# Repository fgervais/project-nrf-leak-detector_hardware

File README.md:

# Leak Detector, revision 3

Any two conductors can be connected to the screw terminals and the alarm will 
start if water shorts them out.

- [Complete Project](#complete-project)
- [PCB](#pcb)
- [Water Probe](#water-probe)
- [Power Consumption](#power-consumption)
- [Firmware](#firmware)
- [Notifications](#notifications)

## Complete Project

### Front side

### Back side

## PCB

### Front side

### Back side

## Water Probe

## Power Consumption

Based on revision [`8f98e931fbc428e85092b7998ec07682605cf380`](https://github.com/fgervais/project-nrf-leak-detector/tree/8f98e931fbc428e85092b7998ec07682605cf380/app/src).

### Idle

How long can the device monitor for a leak?

- Energizer CR2032 = $810 \\, C$
- Idle consumption = $1.09 \\, \frac{{\mu}C}{s}$

```math
\frac{810 \, C}{1.09 \times 10^-6 \, \frac{C}{s}} = 743.119 \times 10^6 \, s
```

```math
470.93 \times 10^6 \, seconds \times \frac{1 \, minute}{60 \, second} \times \frac{1 \, hour}{60 \, minute} \times \frac{1 \, day}{24 \, hour} \times \frac{1 \, year}{365.25 \, days} = 23 \, years
```

Note: This does not account for the battery self discharge and the battery voltage
going down over time.

### Alarm

## Firmware

https://github.com/fgervais/project-nrf-leak-detector

## Notifications

When a leak is detected, the information is sent to Home Assistant tough MQTT
which then sends a notification to computers and mobile devices.

A notification is also sent when the leak detector is reset and rearmed to let
the user know that the leak monitoring is ready.

### Alarm Note

The chain of events from leak detection to a nofication being delivered is
pretty long and a lot could go wrong which would prevent the notification from
being received.

Even though a lot of effort has been put in error handling and retry mechanism,
the focus is to first make sure the alarm starts without being affected by the
notification delivery process.

For this reason, the alarm is setup first before any networking work is started.
Once started, the alarm is entirely handled by the hardware PWM module and so
even if a problem happens the alarm will still be heard.

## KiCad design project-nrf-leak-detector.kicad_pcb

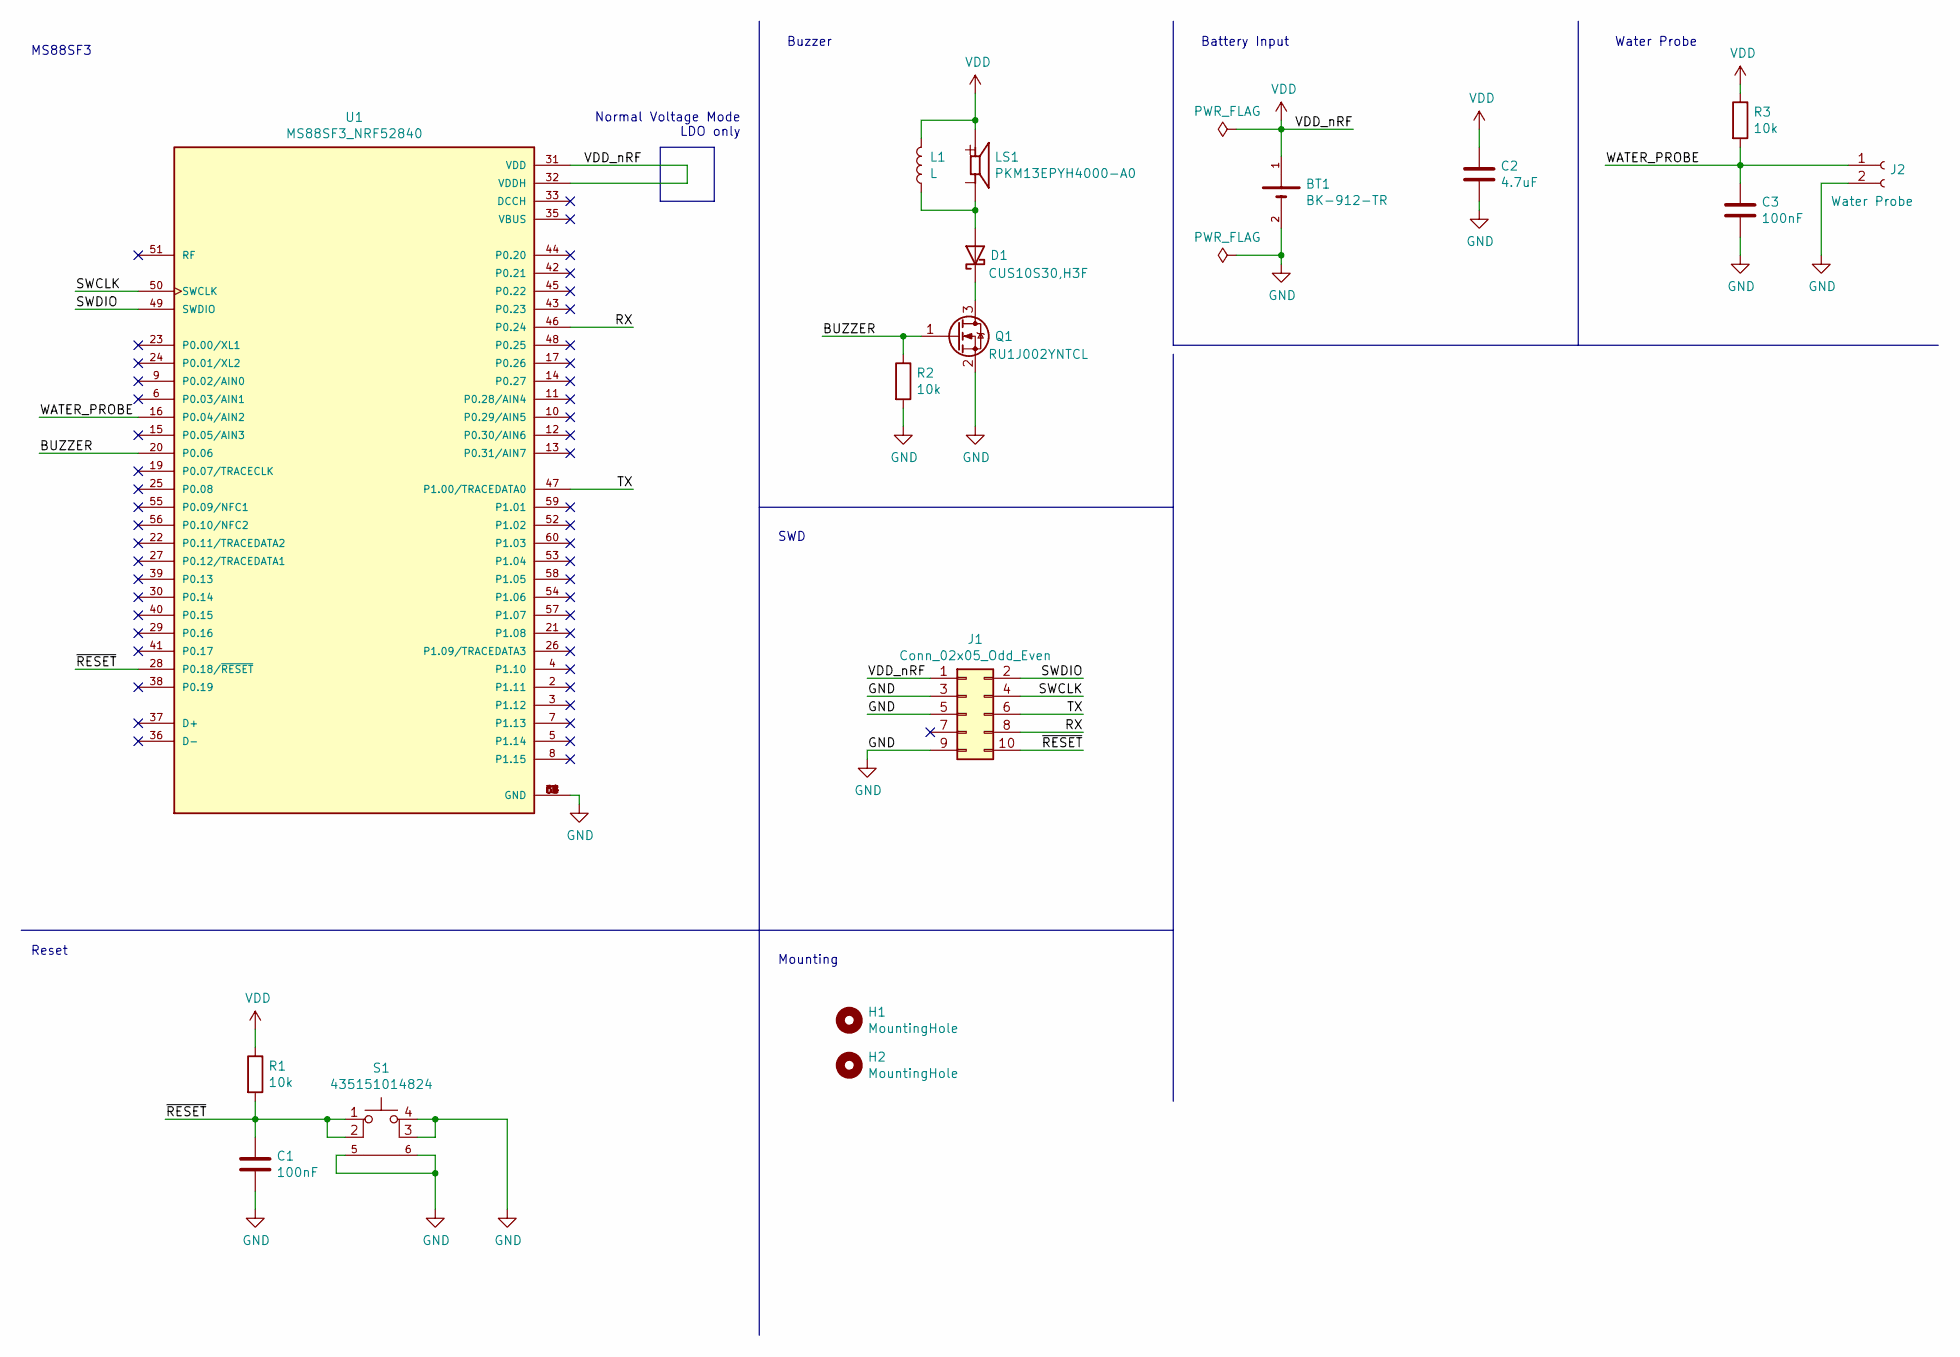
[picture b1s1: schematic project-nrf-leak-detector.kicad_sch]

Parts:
BT1: BK-912-TR; MPD_BK-912-TR; PARTREV H
C1, C3: 100nF; C_0603_1608Metric
C2: 4.7uF; C_0805_2012Metric
D1: D_Schottky; DIO_CUS520,H3F; MPN CUS10S30,H3F
H1, H2: MountingHole; MountingHole_5mm
J1: Conn_02x05_Odd_Even; PinHeader_2x05_P1.27mm_Vertical_SMD
J2: Water Probe; TZ022101B000G
L1: L; INDP7870X750
LS1: PKM13EPYH4000-A0; SPKR_PKM13EPYH4000-A0_SMD; PARTREV December 26, 2017
Q1: Q_NMOS_GSD; SOT-323_SC-70; MPN RU1J002YNTCL
R1, R2, R3: 10k; R_0603_1608Metric
S1: 435151014824; PART-NUMBER 435151014824
U1: MS88SF3_NRF52840; MODULE_MS88SF3_NRF52840; PARTREV V1.1

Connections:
/BUZZER: Q1.1 (G), R2.1, U1.20 (P0.06)
/RX: J1.8, U1.46 (P0.24)
/SWCLK: J1.4, U1.50 (SWCLK)
/SWDIO: J1.2, U1.49 (SWDIO)
/TX: J1.6, U1.47 (P1.00/TRACEDATA0)
/WATER_PROBE: C3.1, J2.1, R3.2, U1.16 (P0.04/AIN2)
/~RESET: C1.1, J1.10, R1.2, S1.1, S1.2, U1.28 (P0.18/~RESET)
GND: BT1.2 (-), C1.2, C2.2, C3.2, J1.3, J1.5, J1.9, J2.2, Q1.2 (S), R2.2, S1.3 (K), S1.4 (A), S1.5, S1.6, U1.1 (GND), U1.18 (GND), U1.34 (GND), U1.61 (GND), U1.62 (GND), U1.63 (GND), U1.64 (GND)
unnamed: D1.1 (K), Q1.3 (D)
unnamed: D1.2 (A), L1.1, LS1.N
VDD: BT1.1 (+), C2.1, J1.1, L1.2, LS1.P, R1.1, R3.1, U1.31 (VDD), U1.32 (VDDH)

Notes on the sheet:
Battery Input
Buzzer
Water Probe
Mounting
MS88SF3
SWD
Normal Voltage Mode LDO only
Reset

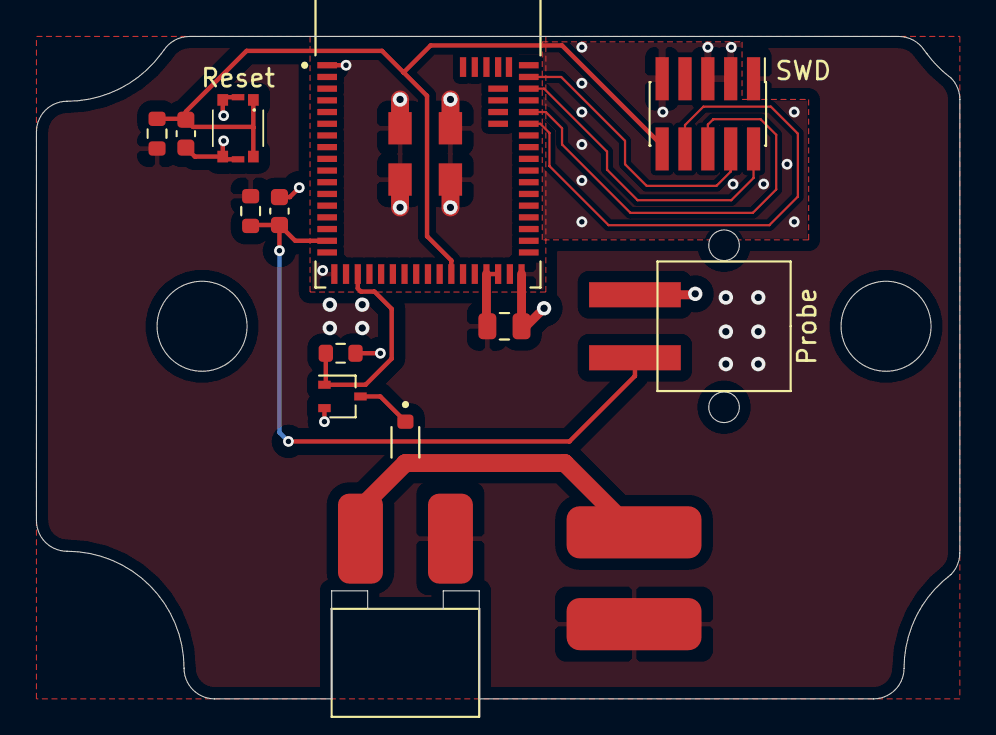
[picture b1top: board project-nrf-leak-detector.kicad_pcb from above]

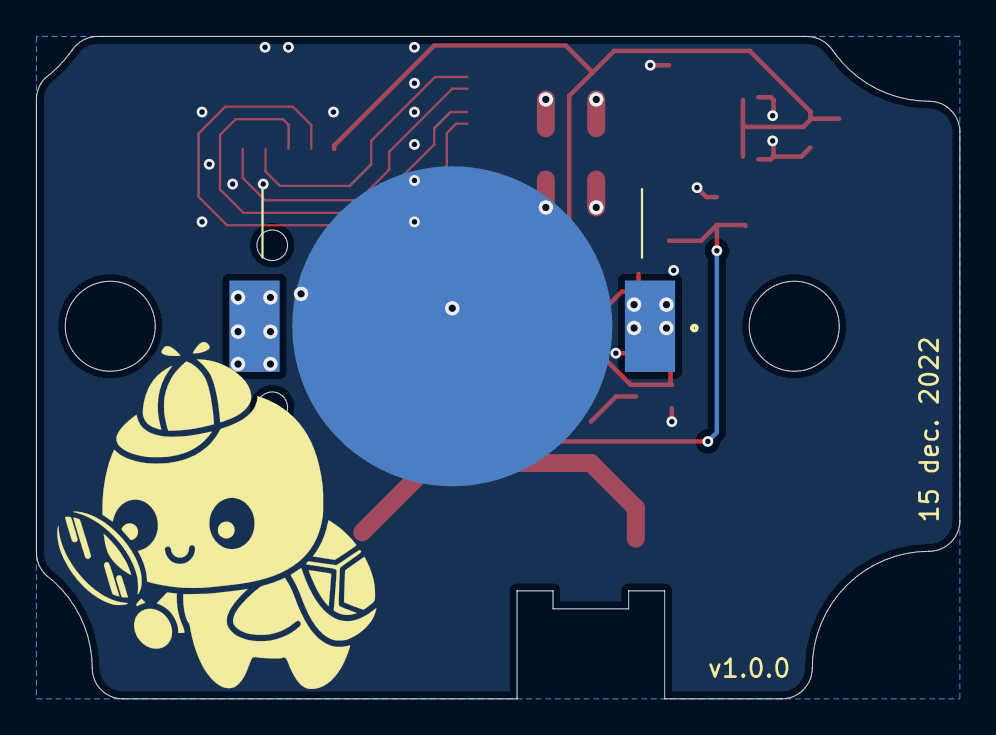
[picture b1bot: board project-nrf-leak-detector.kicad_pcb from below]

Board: 2 copper layers, 51.3 x 36.8 mm, 18 parts (2 on the bottom side), 11 nets.

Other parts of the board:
Ref**: Val**; turtle-01.inverted

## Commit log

2022-11-13 Add all parts to lib
2022-11-14 Remove buzzer-module
2022-11-14 Add an empty main project
2022-11-14 Add rough board outline
2022-11-15 Imported from project-MS88SF3-breakout schematic
2022-11-15 Add a few more components to the schematic
2022-11-16 First schematic version
2022-11-16 Import parts to board
2022-11-17 First placement
2022-11-18 First routing
2022-11-18 Add a 3d model to the TZ022101B000G
2022-11-21 Add info on silkscreen
2022-11-25 Change RX pin to P0.24
    To avoid crossing over TX.
2022-11-26 Add a cap on the probe signal
2022-12-13 Add the turtle
2022-12-15 Change the buzzer slot size and position
2022-12-16 Add gerbers
2022-12-18 Add slot to account for routing bit radius
2022-12-18 Update gerbers
2023-02-26 Ignore backups
2023-02-26 Remove old project file
2023-02-26 Place F.Fab layer
2023-02-27 Add missing part numbers
2023-02-27 Place F.Fab schottky and mosfet
2023-02-27 Add assembly PDF
2023-03-04 Add front and back images
2023-03-04 Update image white balance
2023-03-10 Add pictures of project in enclosure
2023-03-10 Fix table of content
2023-03-10 Add power consumption to README
2023-03-10 Add a short project description
2023-03-14 Correct resistor value error
    10k -> 1M
2023-03-25 Add the water probe image
2024-08-01 Add a notification section
2024-08-01 Limit image width
2024-08-01 Fix wording
2024-08-01 Add a note about the alarm
2024-08-01 Format the alarm note differently
